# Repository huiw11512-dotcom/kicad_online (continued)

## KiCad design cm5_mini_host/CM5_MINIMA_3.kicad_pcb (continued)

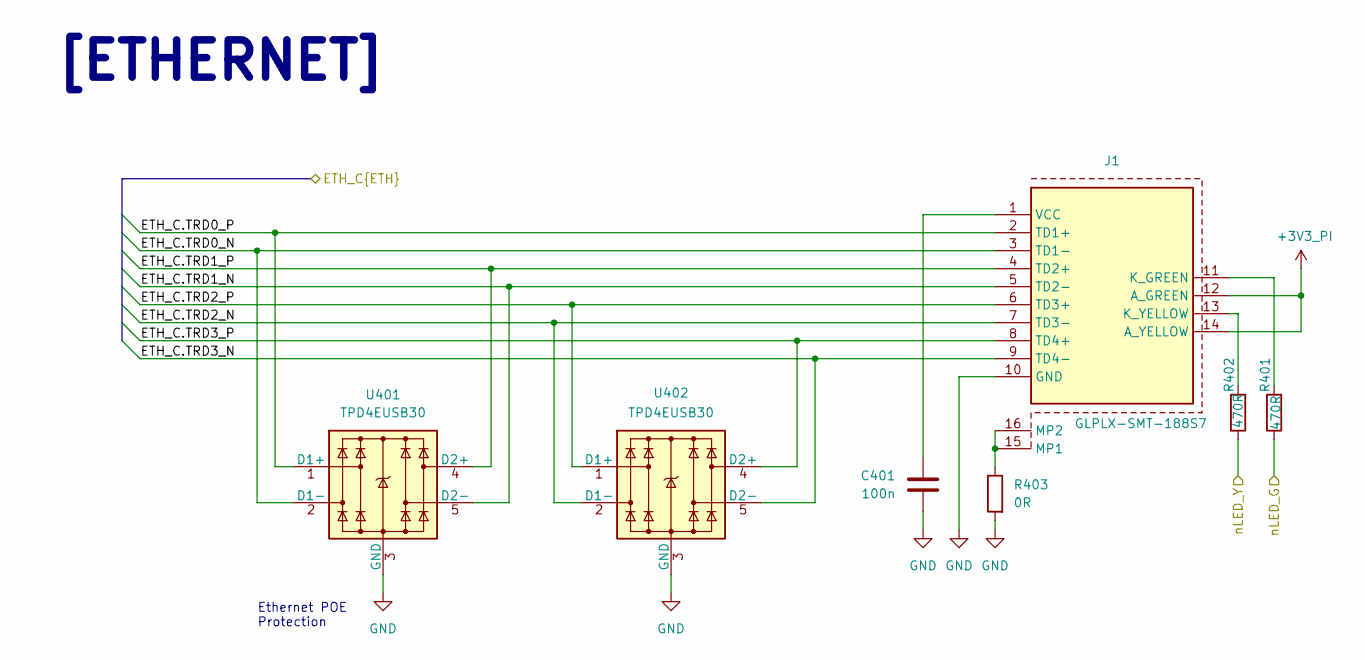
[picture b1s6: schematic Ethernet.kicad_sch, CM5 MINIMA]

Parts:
C401: 100n; C_0402_1005Metric; Part Description 0.1uF 10% 16V Ceramic Capacitor X7R 040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
J1: GLPLX-SMT-188S7; GLPLXSMT188S7QQYG; Manufacturer_Part_Number GLPLX-SMT-188S7-QQ-Y/G; Mouser Part Number 806-GLPLXSMT188S7-YG
R401, R402: 470R; R_0402_1005Metric
R403: 0R; R_0402_1005Metric
U401, U402: TPD4EUSB30; USON-10_2.5x1.0mm_P0.5mm; Part Description Quad TVS diode for high speed signals (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

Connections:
+3V3_PI: J1.12 (A_GREEN), J1.14 (A_YELLOW); also elsewhere on the board
/CM5/ETH_PI.TRD0_N: J1.3 (TD1-), U401.2 (D1-), U401.9; also elsewhere on the board
/CM5/ETH_PI.TRD0_P: J1.2 (TD1+), U401.1 (D1+), U401.10; also elsewhere on the board
/CM5/ETH_PI.TRD1_N: J1.5 (TD2-), U401.5 (D2-), U401.6; also elsewhere on the board
/CM5/ETH_PI.TRD1_P: J1.4 (TD2+), U401.4 (D2+), U401.7; also elsewhere on the board
/CM5/ETH_PI.TRD2_N: J1.7 (TD3-), U402.2 (D1-), U402.9; also elsewhere on the board
/CM5/ETH_PI.TRD2_P: J1.6 (TD3+), U402.1 (D1+), U402.10; also elsewhere on the board
/CM5/ETH_PI.TRD3_N: J1.9 (TD4-), U402.5 (D2-), U402.6; also elsewhere on the board
/CM5/ETH_PI.TRD3_P: J1.8 (TD4+), U402.4 (D2+), U402.7; also elsewhere on the board
/CM5/ETH_nLED_ACTIVITY: R401.1; also elsewhere on the board
/CM5/nLED_SPEED_100_1000: R402.1; also elsewhere on the board
GND: C401.2, J1.10 (GND), R403.2, U401.3 (GND), U401.8 (GND), U402.3 (GND), U402.8 (GND); also elsewhere on the board
unnamed: J1.11 (K_GREEN), R401.2
unnamed: J1.13 (K_YELLOW), R402.2
unnamed: J1.15 (MP1), J1.16 (MP2), R403.1
unnamed: C401.1, J1.1 (VCC)

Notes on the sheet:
[ETHERNET]
Ethernet POE Protection

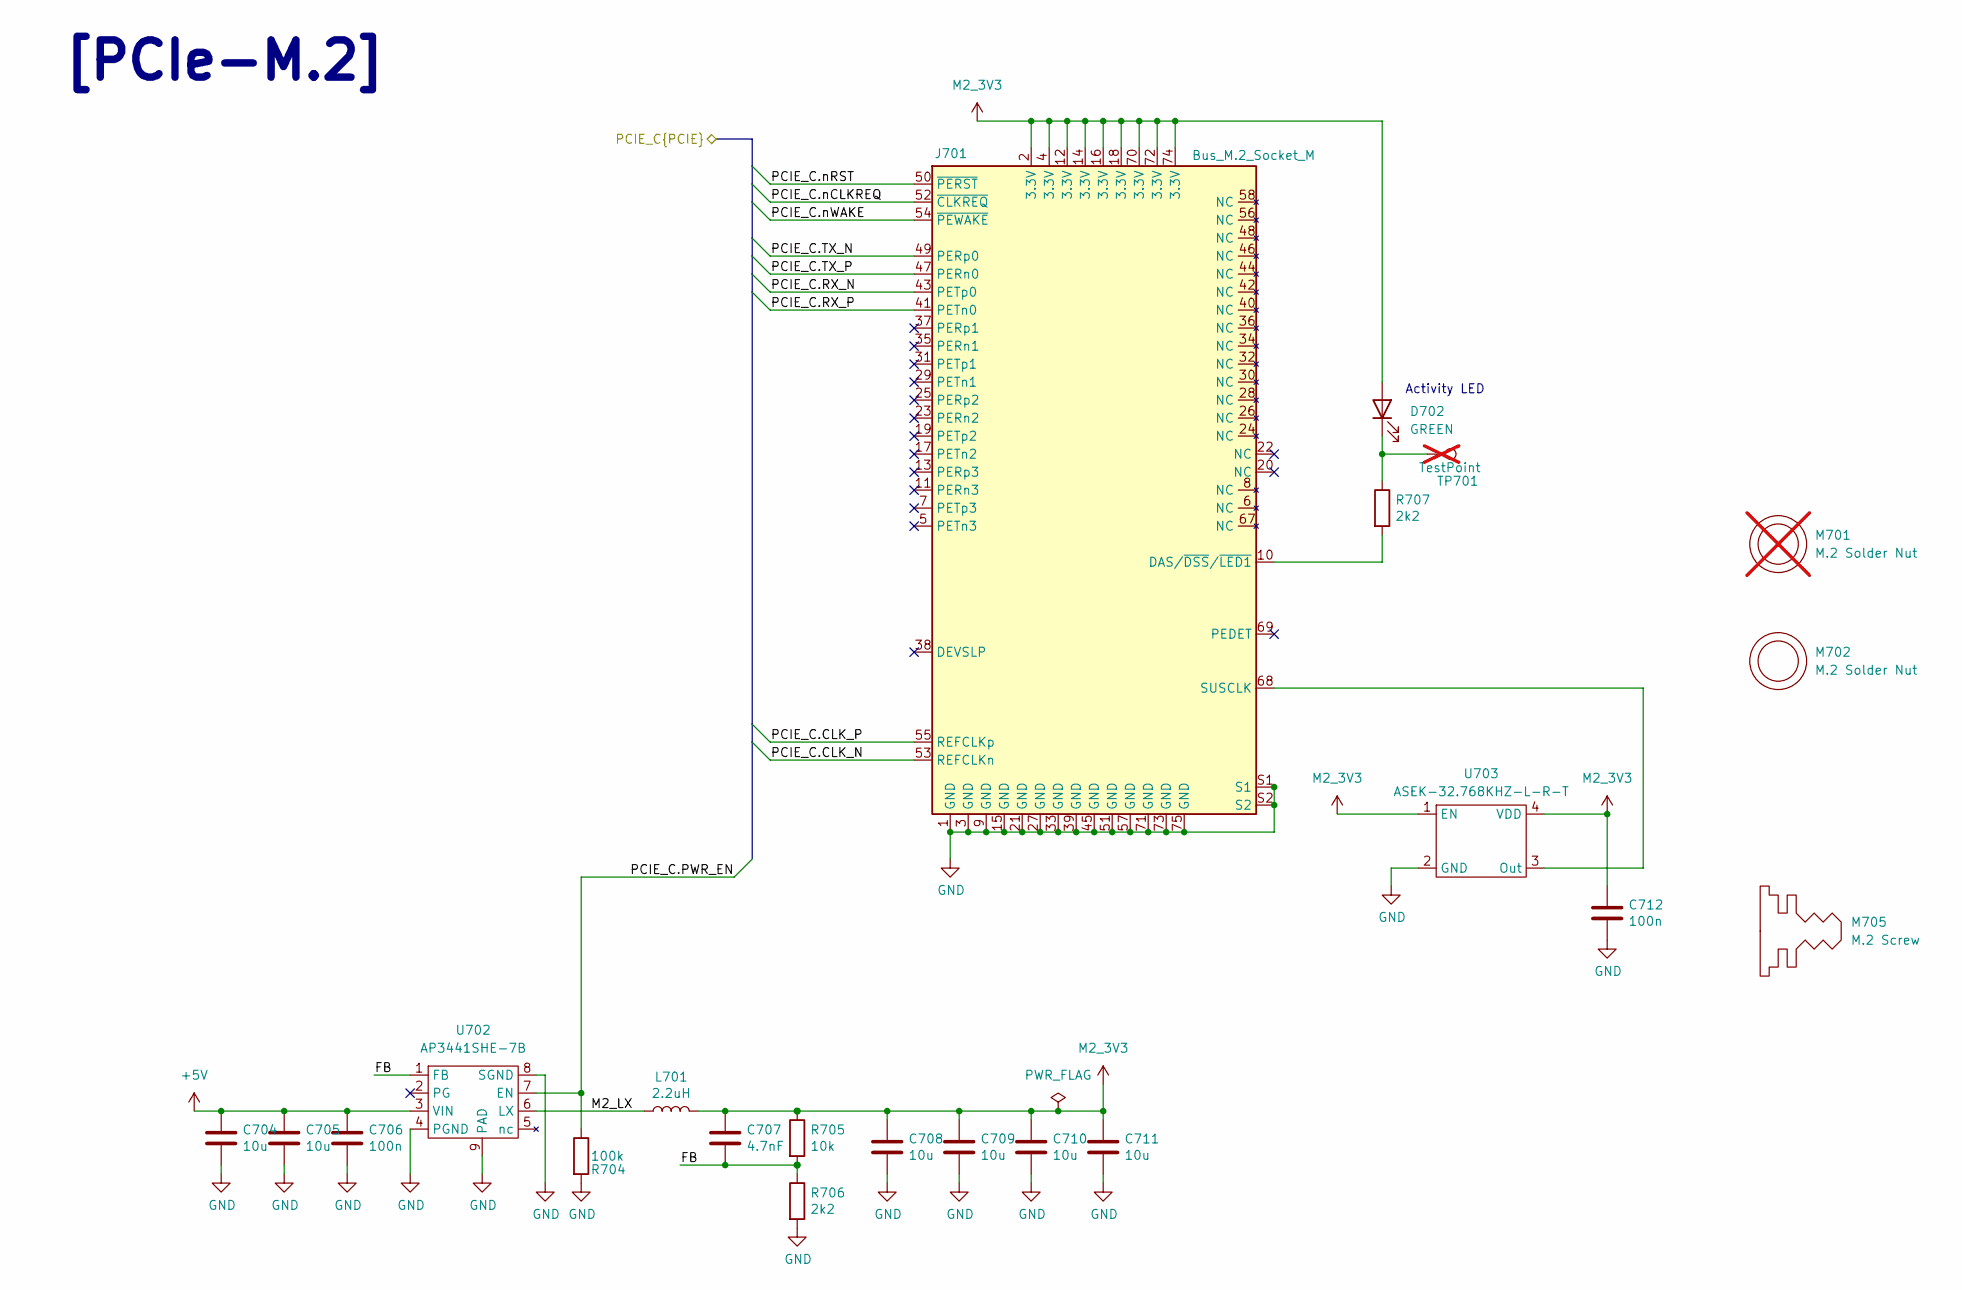
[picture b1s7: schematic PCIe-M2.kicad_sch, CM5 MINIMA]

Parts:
C704, C705, C708, C709, C710, C711: 10u; C_0805_2012Metric; Part Description 10uF 10% 10V Ceramic Capacitor X7R 0805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
C706, C712: 100n; C_0402_1005Metric; Part Description 0.1uF 10% 16V Ceramic Capacitor X7R 040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
C707: 4.7nF; C_0402_1005Metric; Part Description 4.7nF capacitor 0402
D702: GREEN; LED-SMD_L1.7-W0.6-RD
J701: Bus_M.2_Socket_M; M.2 M Key socket_2230_2242; Part Description M.2 M Key connector
L701: 2.2uH; L_Coilcraft_XAL5030-XXX; Part Description Inductor, SMT, 2u2, IRMS=7A, ISAT=8.1A,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
M701: M.2 Solder Nut; MountingHole_3mm_Pad; Part Description Solder nut for M.2 slot; not fitted
M702: M.2 Solder Nut; MountingHole_3mm_Pad; Part Description Solder nut for M.2 slot
M705: M.2 Screw; Part Description M.2 Screw
R704: 100k; R_0402_1005Metric
R705: 10k; R_0402_1005Metric
R706: 2k2; R_0402_1005Metric
R707: 2k2; R_0402_1005Metric; Part Description Resistor 1K M1005 1% 63mW
TP701: TestPoint; Part Description Test point; not fitted
U702: AP3441SHE-7B; DFN-8-1EP_2x2mm_P0.5mm_EP1.05x1.75mm; Part Description 3A DC-DC converter
U703: ASEK-32.768KHZ-L-R-T; Crystal_SMD_3225-4Pin_3.2x2.5mm; Part Description 32KHz Xtal oscilator

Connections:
+5V: C704.1, C705.1, C706.1, U702.3 (VIN); also elsewhere on the board
/CM5/PCIE_PI.CLK_N: J701.53 (REFCLKn); also elsewhere on the board
/CM5/PCIE_PI.CLK_P: J701.55 (REFCLKp); also elsewhere on the board
/CM5/PCIE_PI.PWR_EN: R704.1, U702.7 (EN); also elsewhere on the board
/CM5/PCIE_PI.RX_N: J701.43 (PETp0); also elsewhere on the board
/CM5/PCIE_PI.RX_P: J701.41 (PETn0); also elsewhere on the board
/CM5/PCIE_PI.TX_N: J701.49 (PERp0); also elsewhere on the board
/CM5/PCIE_PI.TX_P: J701.47 (PERn0); also elsewhere on the board
/CM5/PCIE_PI.nCLKREQ: J701.52 (~CLKREQ); also elsewhere on the board
/CM5/PCIE_PI.nRST: J701.50 (~PERST); also elsewhere on the board
/CM5/PCIE_PI.nWAKE: J701.54 (~PEWAKE); also elsewhere on the board
/PCIe-M2/FB: C707.2, R705.2, R706.1, U702.1 (FB)
/PCIe-M2/M2_LX: L701.1, U702.6 (LX)
GND: C704.2, C705.2, C706.2, C708.2, C709.2, C710.2, C711.2, C712.2, J701.1 (GND), J701.3 (GND), J701.9 (GND), J701.15 (GND), J701.21 (GND), J701.27 (GND), J701.33 (GND), J701.39 (GND), J701.45 (GND), J701.51 (GND), J701.57 (GND), J701.71 (GND), J701.73 (GND), J701.75 (GND), J701.S1, J701.S2, R704.2, R706.2, U702.4 (PGND), U702.8 (SGND), U702.9 (PAD), U703.2 (GND); also elsewhere on the board
M2_3V3: C707.1, C708.1, C709.1, C710.1, C711.1, C712.1, D702.2 (A), J701.2 (3.3V), J701.4 (3.3V), J701.12 (3.3V), J701.14 (3.3V), J701.16 (3.3V), J701.18 (3.3V), J701.70 (3.3V), J701.72 (3.3V), J701.74 (3.3V), L701.2, R705.1, U703.1 (EN), U703.4 (VDD)
unnamed: D702.1 (K), R707.1, TP701.1
unnamed: J701.10 (DAS/~DSS/~LED1), R707.2
unnamed: J701.68 (SUSCLK), U703.3 (Out)

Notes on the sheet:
[PCIe-M.2]
Activity LED

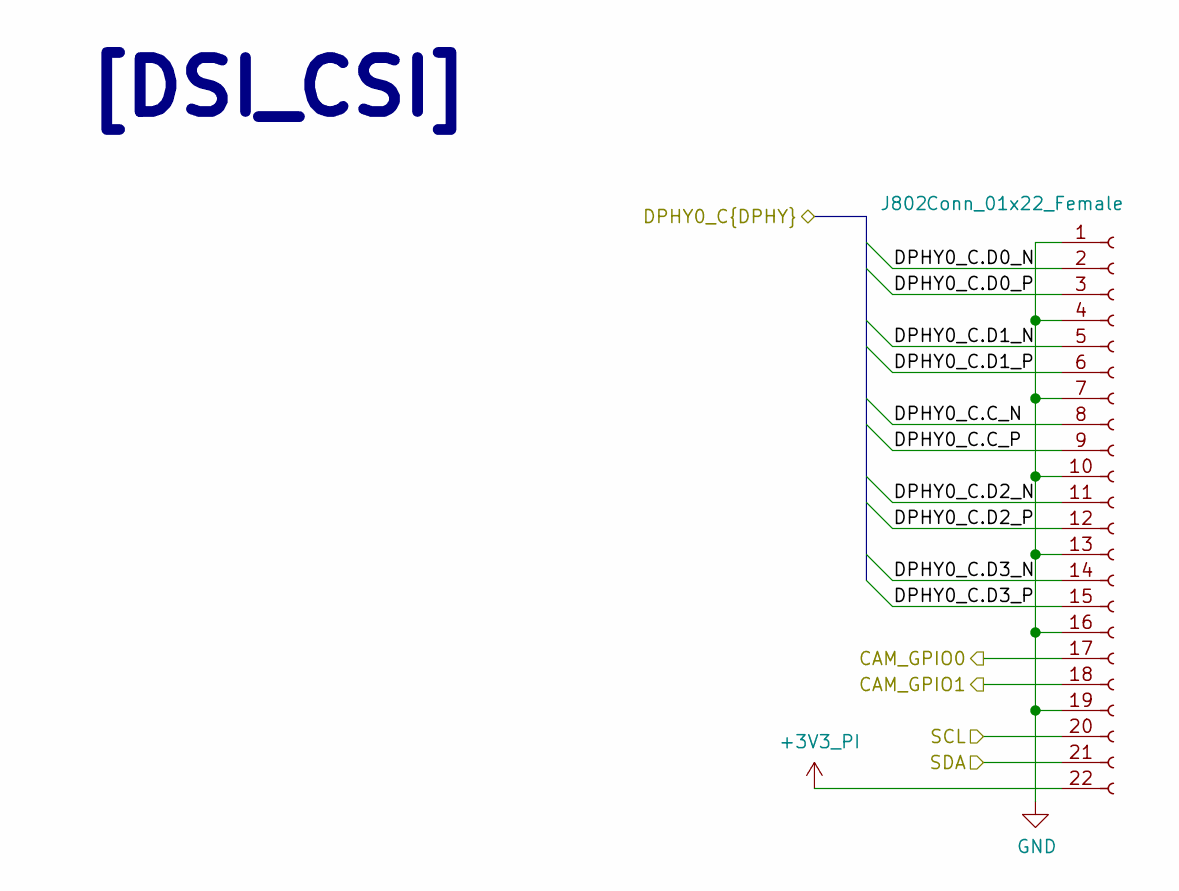
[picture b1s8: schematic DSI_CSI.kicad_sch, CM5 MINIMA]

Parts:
J802: Conn_01x22_Female; Hirose_FH12-22S-0.5SH_1x22-1MP_P0.50mm_Horizontal; Part Description 22 Position FFC, FPC Connector Contacts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

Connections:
+3V3_PI: J802.22; also elsewhere on the board
/CM5/CAM_GPIO0: J802.17; also elsewhere on the board
/CM5/CAM_GPIO1: J802.18; also elsewhere on the board
/CM5/DPHY0_P.C_N: J802.8; also elsewhere on the board
/CM5/DPHY0_P.C_P: J802.9; also elsewhere on the board
/CM5/DPHY0_P.D0_N: J802.2; also elsewhere on the board
/CM5/DPHY0_P.D0_P: J802.3; also elsewhere on the board
/CM5/DPHY0_P.D1_N: J802.5; also elsewhere on the board
/CM5/DPHY0_P.D1_P: J802.6; also elsewhere on the board
/CM5/DPHY0_P.D2_N: J802.11; also elsewhere on the board
/CM5/DPHY0_P.D2_P: J802.12; also elsewhere on the board
/CM5/DPHY0_P.D3_N: J802.14; also elsewhere on the board
/CM5/DPHY0_P.D3_P: J802.15; also elsewhere on the board
/CM5/SCL0: J802.20; also elsewhere on the board
/CM5/SDA0: J802.21; also elsewhere on the board
GND: J802.1, J802.4, J802.7, J802.10, J802.13, J802.16, J802.19; also elsewhere on the board

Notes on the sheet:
[DSI_CSI]

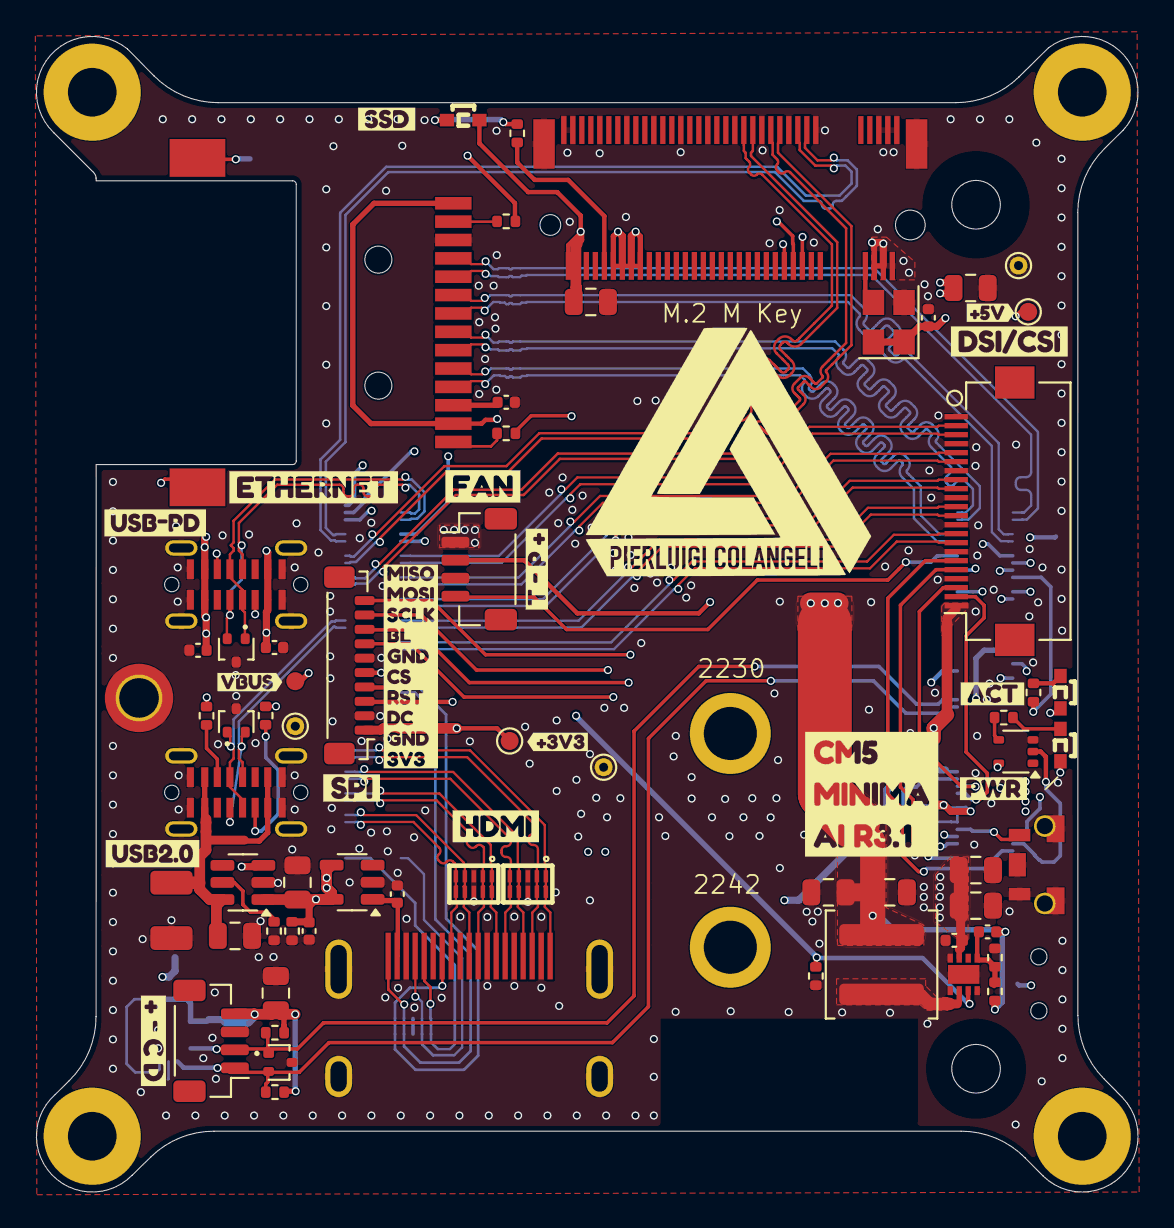
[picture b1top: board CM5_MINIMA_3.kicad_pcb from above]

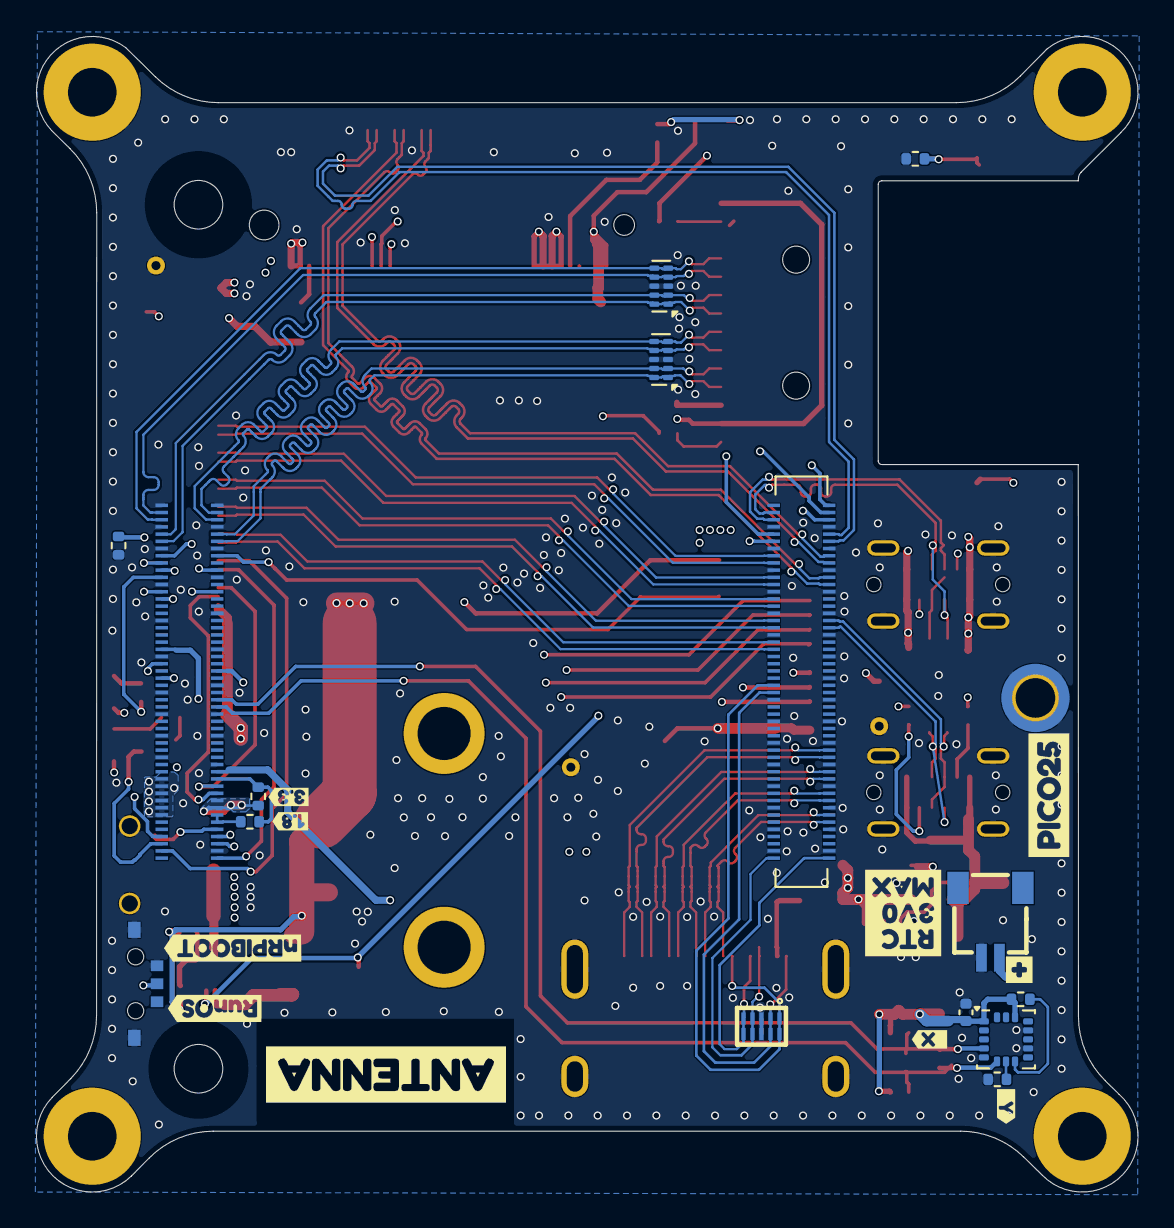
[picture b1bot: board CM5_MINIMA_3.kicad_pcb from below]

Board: 6 copper layers, 61.2 x 64.2 mm, 111 parts (25 on the bottom side), 95 nets.

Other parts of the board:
kibuzzard-67CC6BA6: G***; kibuzzard-67CC6BA6
kibuzzard-67CC6BD3: G***; kibuzzard-67CC6BD3
kibuzzard-67CC6D9E: G***; kibuzzard-67CC6D9E
kibuzzard-67CC6D94: G***; kibuzzard-67CC6D94
kibuzzard-67CC7445: G***; kibuzzard-67CC7445
kibuzzard-67EBAC4C: G***; kibuzzard-67EBAC4C
kibuzzard-67EBB9C1: G***; kibuzzard-67EBB9C1
kibuzzard-67EBD21C: G***; kibuzzard-67EBD21C
kibuzzard-67EBD221: G***; kibuzzard-67EBD221
kibuzzard-67EBEF55: G***; kibuzzard-67EBEF55
kibuzzard-67EBF0A0: G***; kibuzzard-67EBF0A0
kibuzzard-67EBF14E: G***; kibuzzard-67EBF14E
kibuzzard-67EBF015: G***; kibuzzard-67EBF015
kibuzzard-675DA838: G***; kibuzzard-675DA838
kibuzzard-675DA850: G***; kibuzzard-675DA850
kibuzzard-675DA866: G***; kibuzzard-675DA866
kibuzzard-675EDCA4: G***; kibuzzard-675EDCA4
kibuzzard-675EDCB9: G***; kibuzzard-675EDCB9
kibuzzard-6772D327: G***; kibuzzard-6772D327
kibuzzard-6772DA33: G***; kibuzzard-6772DA33
kibuzzard-6773B9CA: G***; kibuzzard-6773B9CA
kibuzzard-6773B9F7: G***; kibuzzard-6773B9F7
kibuzzard-6773BA89: G***; kibuzzard-6773BA89
kibuzzard-6773C2D7: G***; kibuzzard-6773C2D7
kibuzzard-6773C222: G***; kibuzzard-6773C222
kibuzzard-6773C376: G***; kibuzzard-6773C376
kibuzzard-67795592: G***; kibuzzard-67795592

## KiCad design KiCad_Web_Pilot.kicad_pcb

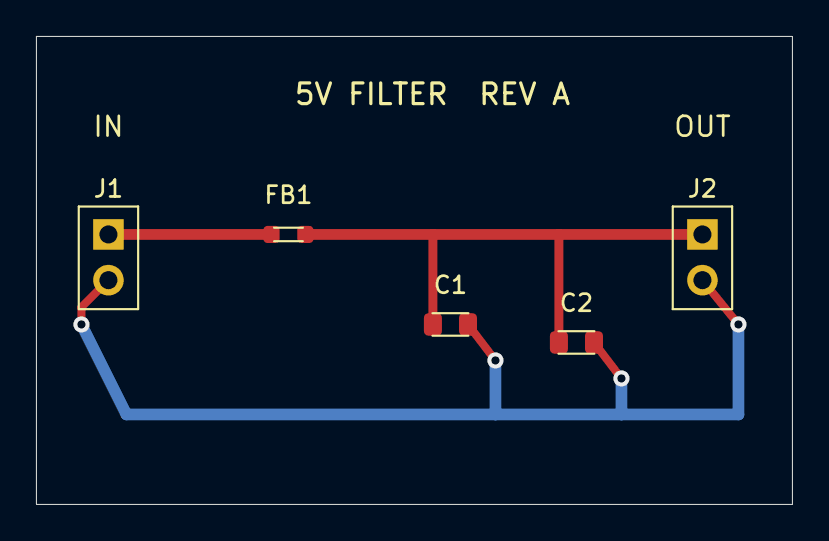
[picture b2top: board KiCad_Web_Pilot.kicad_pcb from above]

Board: 2 copper layers, 42.0 x 26.0 mm, 5 parts (0 on the bottom side), 3 nets.

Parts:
C1: 100nF; C_0805_2012Metric
C2: 10uF; C_0805_2012Metric
FB1: 600R@100MHz; L_0603_1608Metric
J1, J2: Conn_01x02; PinHeader_1x02_P2.54mm_Vertical

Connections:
5V_FILT: C1.1, C2.1, FB1.2, J2.1
GND: C1.2, C2.2, J1.2, J2.2
VIN: FB1.1, J1.1
